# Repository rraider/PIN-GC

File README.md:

PIN-Geigercounter
===

# TODO
- LoRa version, GSM version

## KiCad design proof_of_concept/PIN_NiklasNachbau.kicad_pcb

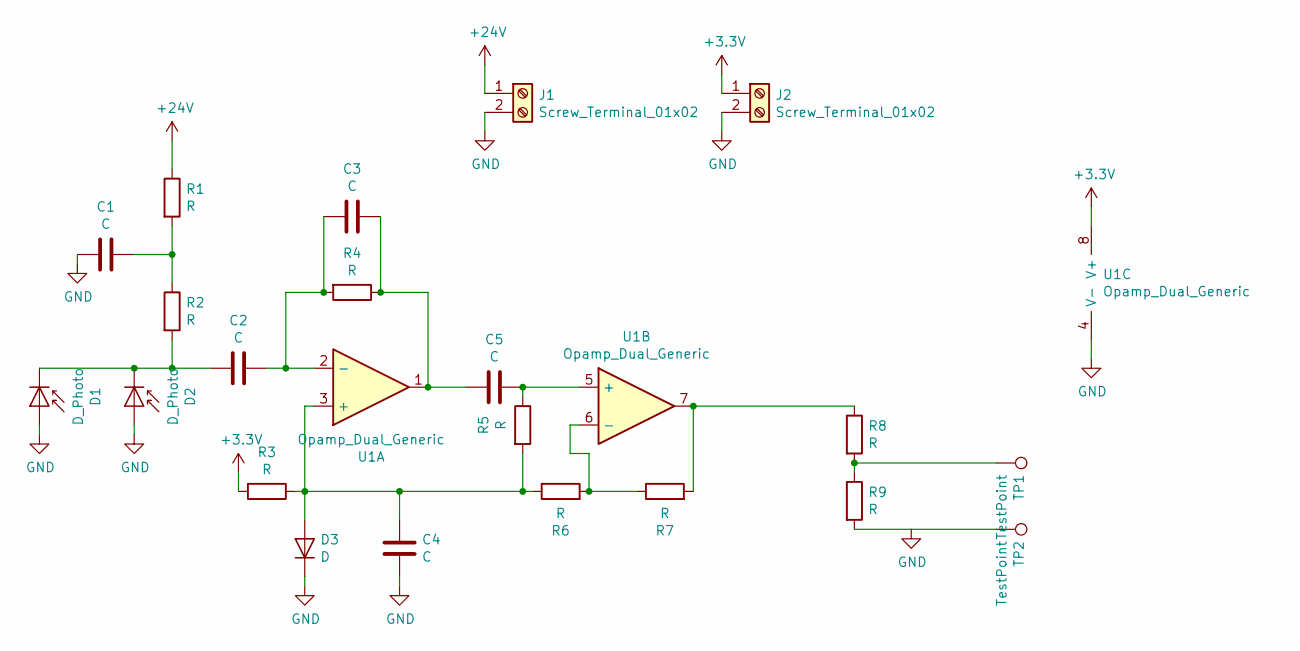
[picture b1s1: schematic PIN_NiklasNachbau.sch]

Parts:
C1, C2, C3, C4, C5: C; C_0805_2012Metric_Pad1.15x1.40mm_HandSolder
D1, D2: D_Photo; Osram_DIL2_4.3x4.65mm_P5.08mm
D3: D; D_DO-35_SOD27_P7.62mm_Horizontal
J1, J2: Screw_Terminal_01x02; TerminalBlock_bornier-2_P5.08mm
R1, R7: R; R_1206_3216Metric_Pad1.42x1.75mm_HandSolder
R2, R3, R4, R5, R6, R8, R9: R; R_0805_2012Metric_Pad1.15x1.40mm_HandSolder
TP1, TP2: TestPoint; TestPoint_Pad_4.0x4.0mm
U1: Opamp_Dual_Generic; SOIC-8_5.23x5.23mm_P1.27mm

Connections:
+3V3: J2.1, R3.2, U1.8 (V+)
+24V: J1.1, R1.1
GND: C1.2, C4.2, D1.2 (A), D2.2 (A), D3.1 (K), J1.2, J2.2, R9.2, TP2.1, U1.4 (V-)
unnamed: C1.1, R1.2, R2.1
unnamed: C2.1, C3.2, R4.2, U1.2 (-)
unnamed: C2.2, D1.1 (K), D2.1 (K), R2.2
unnamed: C3.1, C5.2, R4.1, U1.1
unnamed: C4.1, D3.2 (A), R3.1, R5.2, R6.1, U1.3 (+)
unnamed: C5.1, R5.1, U1.5 (+)
unnamed: R6.2, R7.1, U1.6 (-)
unnamed: R7.2, R8.1, U1.7
unnamed: R8.2, R9.1, TP1.1

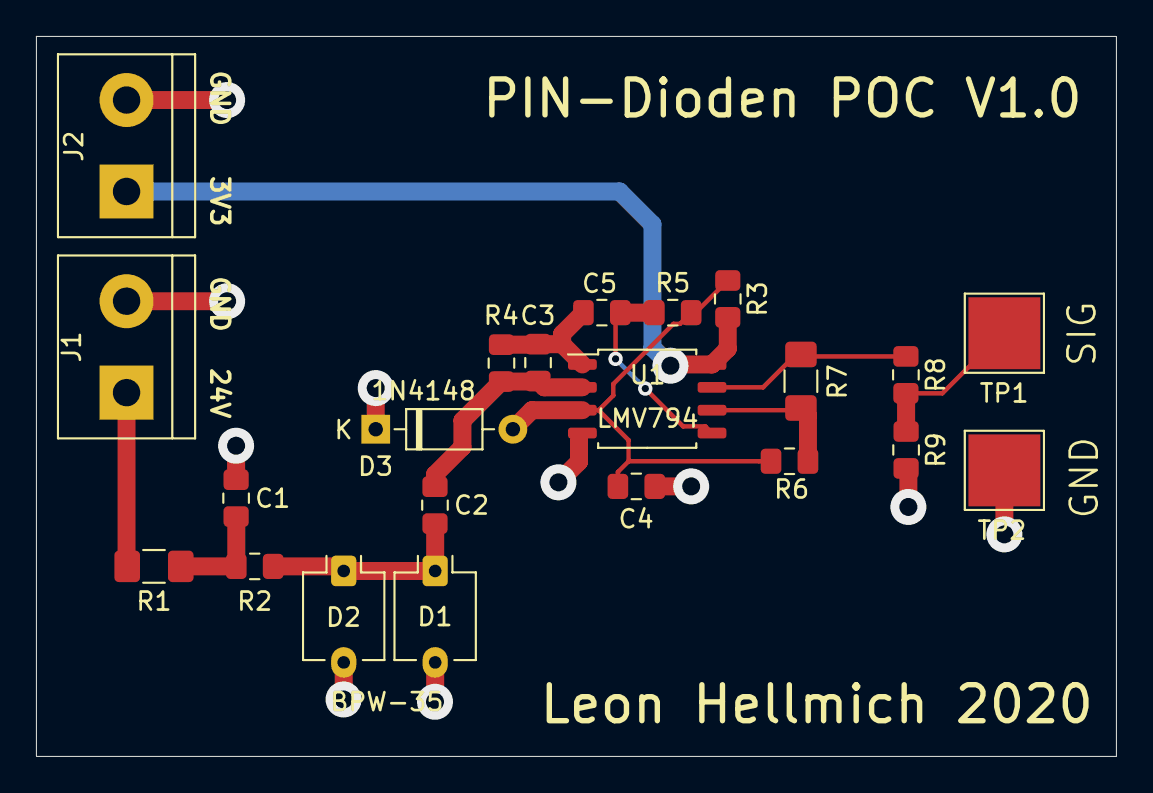
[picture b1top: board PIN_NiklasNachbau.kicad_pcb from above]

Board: 2 copper layers, 60.0 x 40.0 mm, 22 parts (0 on the bottom side), 12 nets.

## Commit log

2019-11-17 Add files via upload
    Schematic made by Niklas Fauth (JugendForscht 2013)
2019-11-17 created project files
2019-11-17 updated schematics
2020-04-11 designed proof of concept pcb
2020-04-11 added sensornode_rev1 project file
